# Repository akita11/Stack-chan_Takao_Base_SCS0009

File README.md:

# Stack-chan_Takao_Base_SCS0009

現時点で ｽﾀｯｸﾁｬﾝ を組み立てる最もシンプルな方法と思われる、[タカオさん](https://twitter.com/mongonta555)の[タカオ版](https://mongonta.booth.pm/)で[Feetech社のシリアルサーボSCS0009](https://www.switch-science.com/products/8042)を使うためのボードです。（※[SCS0009用のタカオ版筐体](https://github.com/mongonta0716/3DPrinter_Models)とあわせて使用できます。M5Stack本体と2個のシリアルサーボモータSCS0009用コネクタ、給電用のUSB TypeCコネクタがついたボードです。電源スイッチもついています。まるごと一式、タカオ版のサーボ固定部分(Bracket)に収納できます。市販のUSB Type-CコネクタつきのACアダプタ等をつないで給電して使用します。以下のように、本体の後ろ側からUSB Type-Cケーブルで給電して動作させることができます。

## 表面実装部品版

※完成品として[スイッチサイエンスで委託販売中](https://www.switch-science.com/products/9288)です

## 挿入実装部品版

※部品キットとして[スイッチサイエンスで委託販売中](https://www.switch-science.com/products/9289)です

※部品キット版では、[組み立て手順](https://github.com/akita11/Stack-chan_Takao_Base_SCS0009/blob/main/Build/README.md)に沿って部品をはんだ付けしてください。

## 他に用意するもの

- M5Stack本体 (Core BasicまたはCore2がおすすめ）
- シリアルサーボモータ2個 [Feetech SCS0009](https://www.switch-science.com/products/8042)
- Groveケーブル ([M5Stack用5cm](https://www.switch-science.com/products/8664)など。すでにM5StackのUNITなどで余っているものがあればそれでもOK）
- 筐体[SCS0009用のタカオ版筐体](https://github.com/mongonta0716/3DPrinter_Models)を3Dプリント出力したものと必要なネジ類（[Boothで頒布中](https://booth.pm/ja/items/5186064)）

## 使い方

- 筐体の組み立てなどは、[タカオさんの手順](https://booth.pm/ja/items/5186064)を参考に行います。
- M5Stack本体と本ボードはGroveケーブルで接続します
- 2個のサーボを本ボードに接続します。ボード上の「H1」側には水平方向（足側）のサーボを、「V2」側には上下方向（筐体側）のサーボを接続します。いずれも、サーボのGND側（茶色や黒のケーブル側）を、本ボードの端側（白マークのある側）に挿し込みます。
- 本ボードを、Bracket（サーボを固定している部品）に収めます。必要に応じて両面テープやネジなどで固定してください。

## シリアルサーボSCS0009の設定

Feetech社のシリアルサーボSCS0009は、専用設定ツール[FD](https://gitee.com/ftservo/fddebug)を使ってIDや各種パラメータを設定することができます。特に今回のように2個のSCS0009を別々に使用する場合はそれぞれにIDを設定する必要があります。IDの初期値は1ですので、1つのSCC0009のIDを2に設定する必要があります。SCS0009の設定には[純正のボードFE-URT-1](https://akizukidenshi.com/catalog/g/gM-16295/)を使うこともできますが、このStack-chan_TakaoBaSE_SCS0009は簡易的に設定をするための回路が組み込まれています。ただし簡易的な回路のため、設定の読み出し・書き込みに失敗することもありますので、うまく読み出し・書き込みができない場合は、何度かリトライしてください。
※この回路は、[@washishi](https://twitter.com/washishi)さんの[Xでの投稿](https://twitter.com/washishi/status/1589990730822725632)を参考にしました。

M5Stack(Basic/Core2)、本ボード、IDを変更するSCS0009（どちらのコネクタでもOK）を接続する。M5Stackには、設定用プログラムを書き込んでおく。（フォルダSCS0009testをVisualStudioCodeで開き、PlatformIOでビルド・書き込みする。必要に応じてplatformio.iniのボード指定を変更する（標準ではCore2用で、[env]内のdefault_envsで切り替え可能））

M5StackをPCに接続し、BaudRateを115,200を選んでそのCOMポートを開く。その後、”Search"を押すと、接続されているSCS0009が現れる（※出てこない場合はリトライしたり、USBケーブル抜き差しやM5Stackのリセット後にリトライする）

ID=1のSCS0009が見つかるはずなので、それを選択し、"Progamming"タブ内を開く。その中の"5.ID"を選ぶと、右下にIDを設定するボックスが現れるので、ここに"2"を入力して"Save"する。

正しくIDが設定されればOK。念のため再度"Search"して、ID=2のSCS0009が見つかることを確認する。設定エラーが出る場合はリトライする。

## Author

Junichi Akita (akita@ifdl.jp, @akita11)

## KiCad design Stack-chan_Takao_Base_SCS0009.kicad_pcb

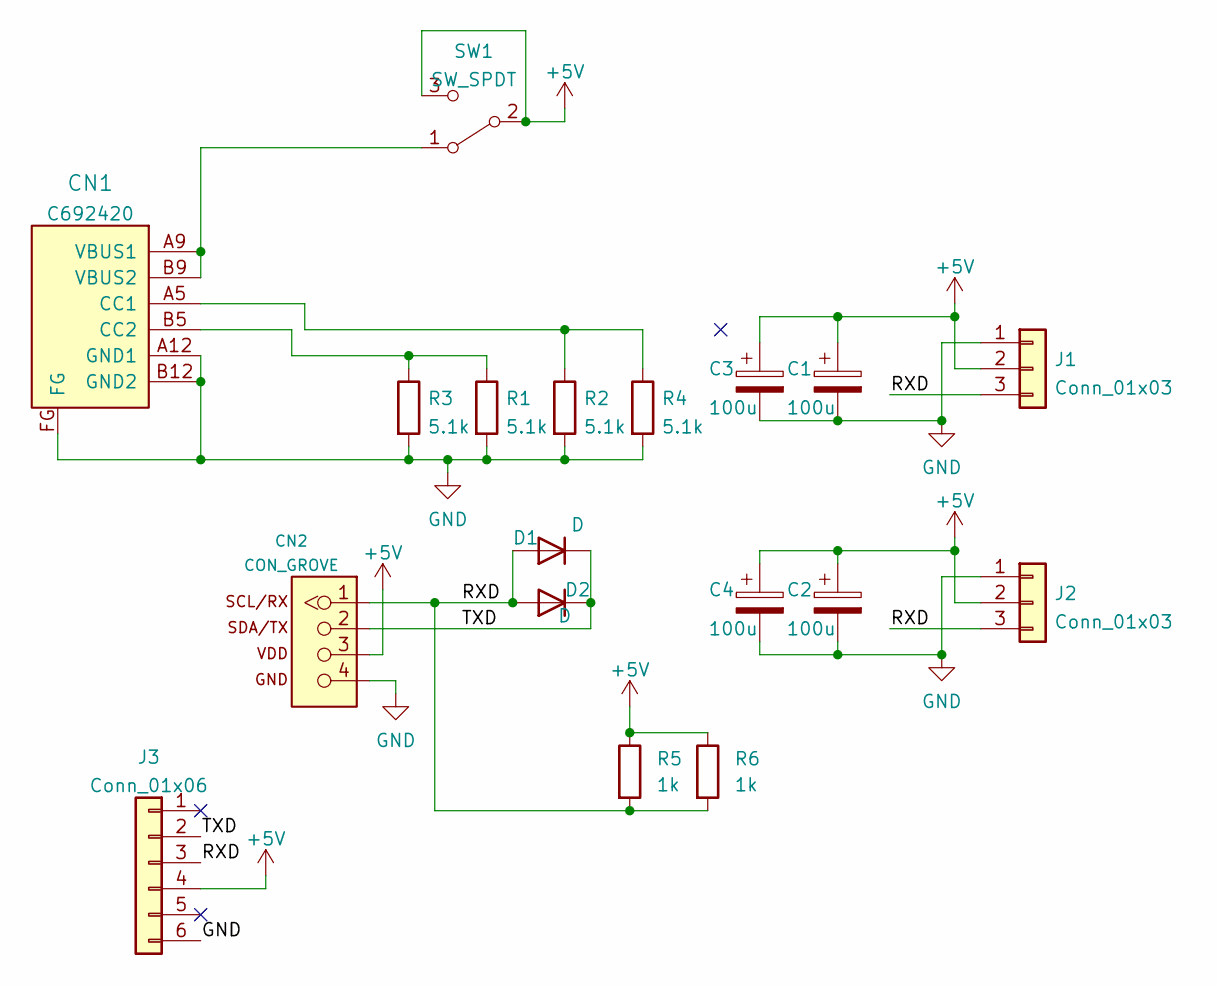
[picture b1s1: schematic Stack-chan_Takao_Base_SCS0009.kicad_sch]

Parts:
C1, C2: 100u; CP_Radial_D6.3mm_P2.50mm
C3, C4: 100u; C_1206_3216Metric
CN1: CON_USB-C-6; USB-C_6P_V_TH; LCSC C692420
CN2: CON_GROVE; CON_GROVE_V
D1: D; D_SOD-123F
D2: D; D_DO-34_SOD68_P7.62mm_Horizontal
J1, J2: Conn_01x03; Molex_SPOX_5267-03A_1x03_P2.50mm_Vertical
J3: Conn_01x06; PinSocket_1x06_P2.54mm_Vertical
R1, R2: 5.1k; R_0603_1608Metric
R3, R4: 5.1k; R_Axial_DIN0204_L3.6mm_D1.6mm_P5.08mm_Vertical
R5: 1k; R_Axial_DIN0204_L3.6mm_D1.6mm_P5.08mm_Vertical
R6: 1k; R_0603_1608Metric
SW1: SW_SPDT; SW_SPDT_9x4mm_W2.5mm

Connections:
+5V: C1.1, C2.1, C3.1, C4.1, CN2.3, J1.2, J2.2, J3.4, R5.1, R6.1, SW1.2 (B), SW1.3 (C)
/RXD: CN2.1, D1.2 (A), D2.2 (A), J1.3, J2.3, J3.3, R5.2, R6.2
/TXD: CN2.2, D1.1 (K), D2.1 (K), J3.2
GND: C1.2, C2.2, C3.2, C4.2, CN1.A12 (GND1), CN1.B12 (GND2), CN1.FG, CN2.4, J1.1, J2.1, J3.6, R1.2, R2.2, R3.2, R4.2
unnamed: CN1.A5 (CC1), R2.1, R4.1
unnamed: CN1.A9 (VBUS1), CN1.B9 (VBUS2), SW1.1 (A)
unnamed: CN1.B5 (CC2), R1.1, R3.1

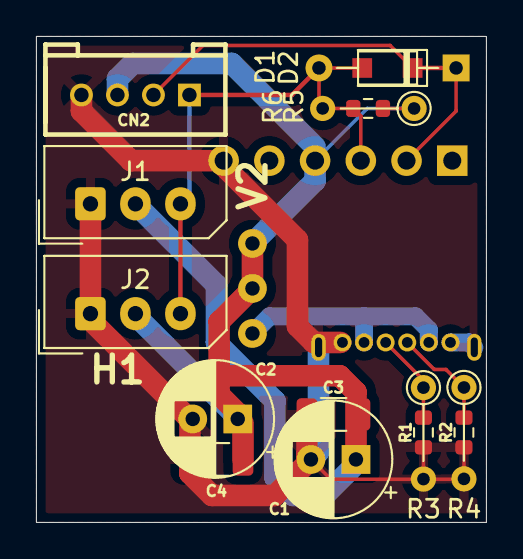
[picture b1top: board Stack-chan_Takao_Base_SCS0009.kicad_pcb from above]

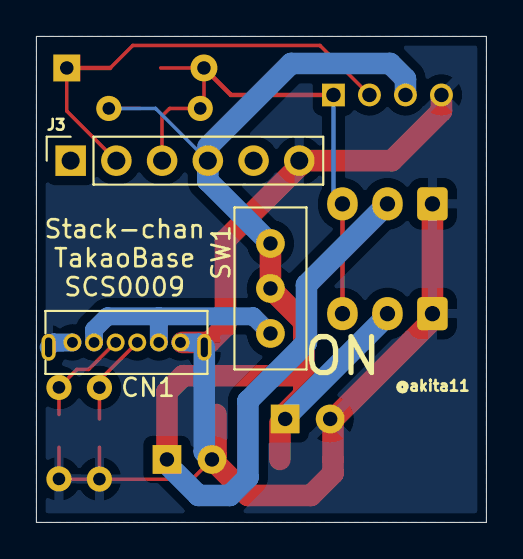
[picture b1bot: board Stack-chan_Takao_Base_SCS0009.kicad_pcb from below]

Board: 2 copper layers, 25.0 x 27.0 mm, 18 parts (3 on the bottom side), 7 nets.

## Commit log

2023-10-10 update photos and readme
2023-10-10 fix typo
2023-10-30 Support M5Unified
2023-11-11 for ATOM
